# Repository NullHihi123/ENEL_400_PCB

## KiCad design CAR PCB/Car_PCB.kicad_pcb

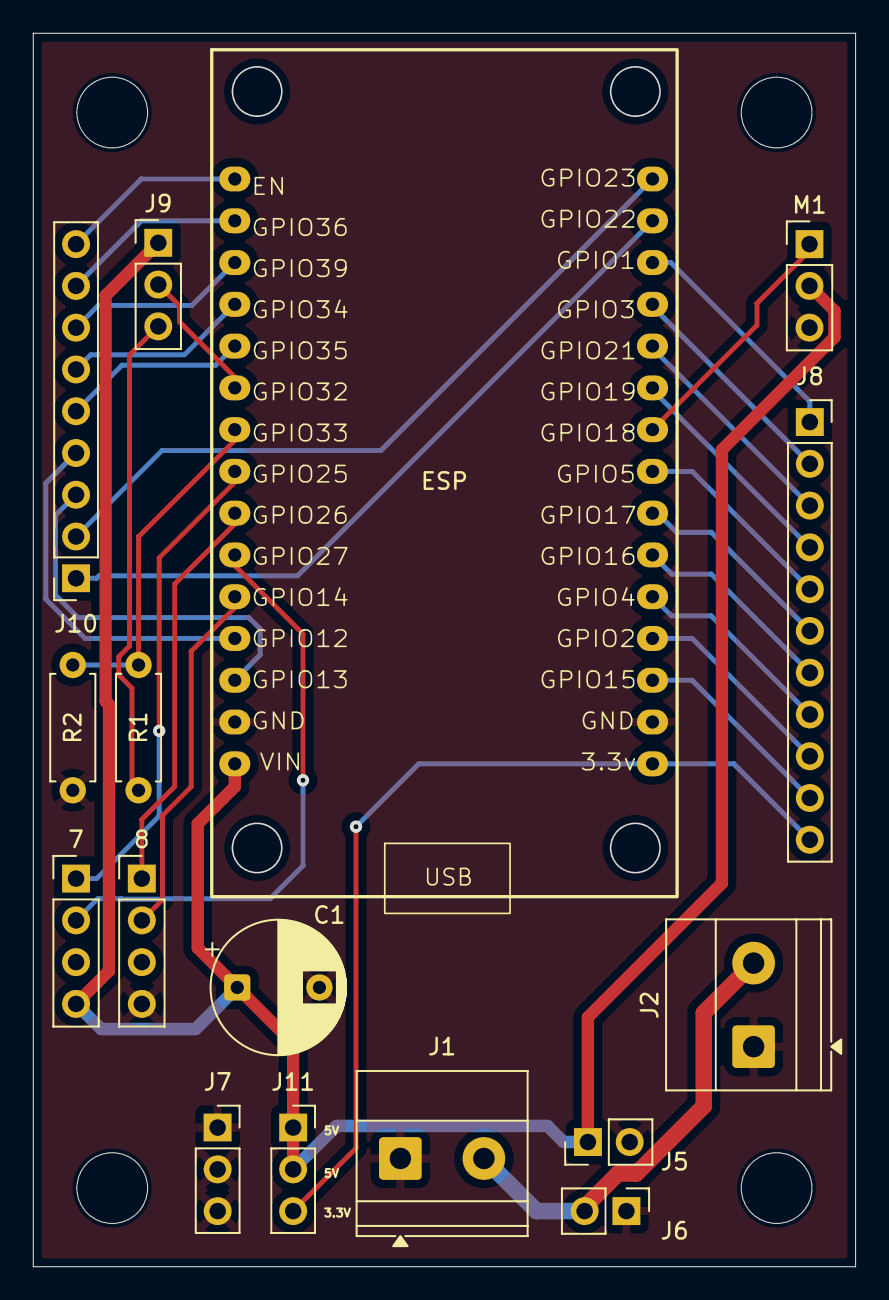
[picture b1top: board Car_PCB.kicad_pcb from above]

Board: 2 copper layers, 50.0 x 75.0 mm, 20 parts (0 on the bottom side), 31 nets.

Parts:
7: BTS Logic 7; PinHeader_1x04_P2.54mm_Vertical
8: BTS Logic 8; PinHeader_1x04_P2.54mm_Vertical
C1: 10uF; CP_Radial_D8.0mm_P5.00mm
ESP: ESP32_30pin
J1: Battery Input (VIN); TerminalBlock_Phoenix_MKDS-1,5-2-5.08_1x02_P5.08mm_Horizont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
J2: Battery to motor driver; TerminalBlock_Phoenix_MKDS-1,5-2-5.08_1x02_P5.08mm_Horizont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
J5: Buck Reg (5V); PinHeader_1x02_P2.54mm_Vertical
J6: BAT to BUCK (11.1-5V); PinHeader_1x02_P2.54mm_Vertical
J7: GND; PinSocket_1x03_P2.54mm_Vertical
J8: Spare Pins 2; PinSocket_1x11_P2.54mm_Vertical
J9: Distance sensor; PinHeader_1x03_P2.54mm_Vertical
J10: Spare Pins 1; PinSocket_1x09_P2.54mm_Vertical
J11: Vdd; PinSocket_1x03_P2.54mm_Vertical
M1: Motor_Servo; PinHeader_1x03_P2.54mm_Vertical
MH1, MH2, MH3, MH4: MountingHole_4.3mm_M4_ISO7380
R1: 10K; R_Axial_DIN0207_L6.3mm_D2.5mm_P7.62mm_Horizontal
R2: 20K; R_Axial_DIN0207_L6.3mm_D2.5mm_P7.62mm_Horizontal

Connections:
/5V Power: 7.4, C1.1, ESP.1 (VIN), J5.1, J9.1, J11.1, J11.2, M1.2 (+)
/Battery Power: J1.2, J2.2, J6.2
GND: 8.4, C1.2, ESP.2 (GND), ESP.17 (GND), J1.1, J2.1, J5.2, J6.1, J7.1, J7.2, J7.3, M1.3 (-), R2.2
unnamed: 7.1, ESP.8 (GPIO25)
unnamed: 7.2, ESP.6 (GPIO27)
unnamed: 8.1, ESP.7 (GPIO26)
unnamed: 8.2, ESP.5 (GPIO14)
unnamed: ESP.28 (GPIO1), J8.1
unnamed: ESP.27 (GPIO3), J8.2
unnamed: ESP.26 (GPIO21), J8.3
unnamed: ESP.25 (GPIO19), J8.4
unnamed: ESP.23 (GPIO5), J8.5
unnamed: ESP.22 (GPIO17), J8.6
unnamed: ESP.21 (GPIO16), J8.7
unnamed: ESP.20 (GPIO4), J8.8
unnamed: ESP.19 (GPIO2), J8.9
unnamed: ESP.18 (GPIO15), J8.10
unnamed: ESP.10 (GPIO32), J9.2
unnamed: J9.3, R1.1
unnamed: ESP.29 (GPIO22), J10.1
unnamed: ESP.30 (GPIO23), J10.2
unnamed: ESP.3 (GPIO13), J10.3
unnamed: ESP.4 (GPIO12), J10.4
unnamed: ESP.11 (GPIO35), J10.5
unnamed: ESP.12 (GPIO34), J10.6
unnamed: ESP.13 (GPIO39), J10.7
unnamed: ESP.14 (GPIO36), J10.8
unnamed: ESP.15 (EN), J10.9
unnamed: ESP.16 (3.3v), J8.11, J11.3
unnamed: ESP.24 (GPIO18), M1.1 (PWM)
unnamed: ESP.9 (GPIO33), R1.2, R2.1

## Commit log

2026-02-11 Create tml
2026-02-11 Org Push
2026-02-11 Org Folder
